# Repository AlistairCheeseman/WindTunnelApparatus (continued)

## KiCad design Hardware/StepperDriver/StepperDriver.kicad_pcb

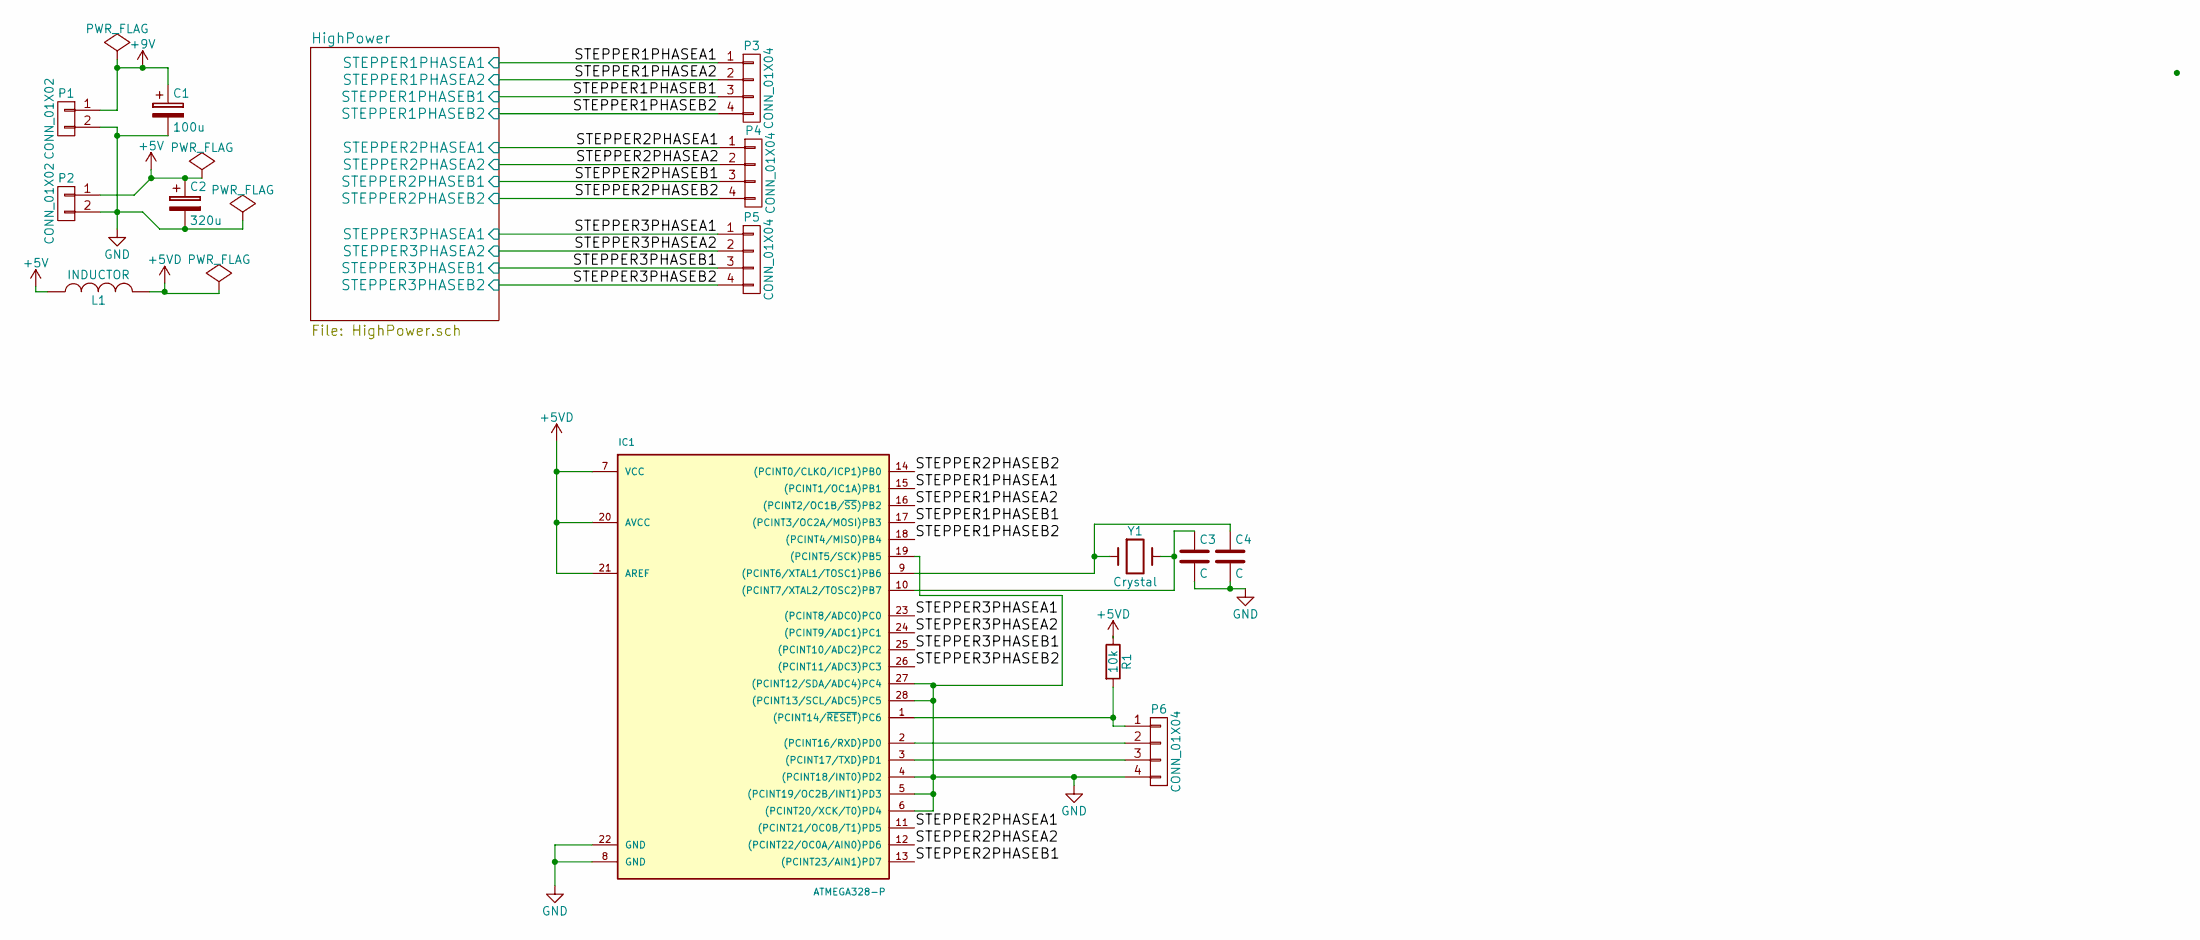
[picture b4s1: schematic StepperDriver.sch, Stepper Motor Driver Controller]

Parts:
C1: 100u; C_Radial_D10_L20_P7.5
C2: 320u; C_Radial_D10_L20_P7.5
C3, C4: C; C_Disc_D3_P2.5
IC1: ATMEGA328-P; DIP-28_W7.62mm_LongPads
L1: INDUCTOR; Neosid_Inductor_Sd12k-style3
P1, P2: CONN_01X02; TerminalBlock_Pheonix_MPT-2.54mm_2pol
P3, P4, P5, P6: CONN_01X04; TerminalBlock_Pheonix_MPT-2.54mm_4pol
R1: 10k; Resistor_Horizontal_RM10mm
Y1: Crystal; Crystal_HC48-U_Vertical

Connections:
+5V: C2.1, L1.1, P2.1; also elsewhere on the board
+5VD: IC1.7 (VCC), IC1.20 (AVCC), IC1.21 (AREF), L1.2, R1.1
+9V: C1.1, P1.1; also elsewhere on the board
/HighPower/STEPPER1PHASEA1: IC1.15 ((PCINT1/OC1A)PB1), P3.1; also elsewhere on the board
/HighPower/STEPPER1PHASEA2: IC1.16 ((PCINT2/OC1B/~SS~)PB2), P3.2; also elsewhere on the board
/HighPower/STEPPER1PHASEB1: IC1.17 ((PCINT3/OC2A/MOSI)PB3), P3.3; also elsewhere on the board
/HighPower/STEPPER1PHASEB2: IC1.18 ((PCINT4/MISO)PB4), P3.4; also elsewhere on the board
/HighPower/STEPPER2PHASEA1: IC1.11 ((PCINT21/OC0B/T1)PD5), P4.1; also elsewhere on the board
/HighPower/STEPPER2PHASEA2: IC1.12 ((PCINT22/OC0A/AIN0)PD6), P4.2; also elsewhere on the board
/HighPower/STEPPER2PHASEB1: IC1.13 ((PCINT23/AIN1)PD7), P4.3; also elsewhere on the board
/HighPower/STEPPER2PHASEB2: IC1.14 ((PCINT0/CLKO/ICP1)PB0), P4.4; also elsewhere on the board
/HighPower/STEPPER3PHASEA1: IC1.23 ((PCINT8/ADC0)PC0), P5.1; also elsewhere on the board
/HighPower/STEPPER3PHASEA2: IC1.24 ((PCINT9/ADC1)PC1), P5.2; also elsewhere on the board
/HighPower/STEPPER3PHASEB1: IC1.25 ((PCINT10/ADC2)PC2), P5.3; also elsewhere on the board
/HighPower/STEPPER3PHASEB2: IC1.26 ((PCINT11/ADC3)PC3), P5.4; also elsewhere on the board
GND: C1.2, C2.2, C3.2, C4.2, IC1.4 ((PCINT18/INT0)PD2), IC1.5 ((PCINT19/OC2B/INT1)PD3), IC1.6 ((PCINT20/XCK/T0)PD4), IC1.8 (GND), IC1.19 ((PCINT5/SCK)PB5), IC1.22 (GND), IC1.27 ((PCINT12/SDA/ADC4)PC4), IC1.28 ((PCINT13/SCL/ADC5)PC5), P1.2, P2.2, P6.4; also elsewhere on the board
unnamed: C3.1, IC1.10 ((PCINT7/XTAL2/TOSC2)PB7), Y1.2
unnamed: C4.1, IC1.9 ((PCINT6/XTAL1/TOSC1)PB6), Y1.1
unnamed: IC1.1 ((PCINT14/~RESET~)PC6), P6.1, R1.2
unnamed: IC1.2 ((PCINT16/RXD)PD0), P6.2
unnamed: IC1.3 ((PCINT17/TXD)PD1), P6.3

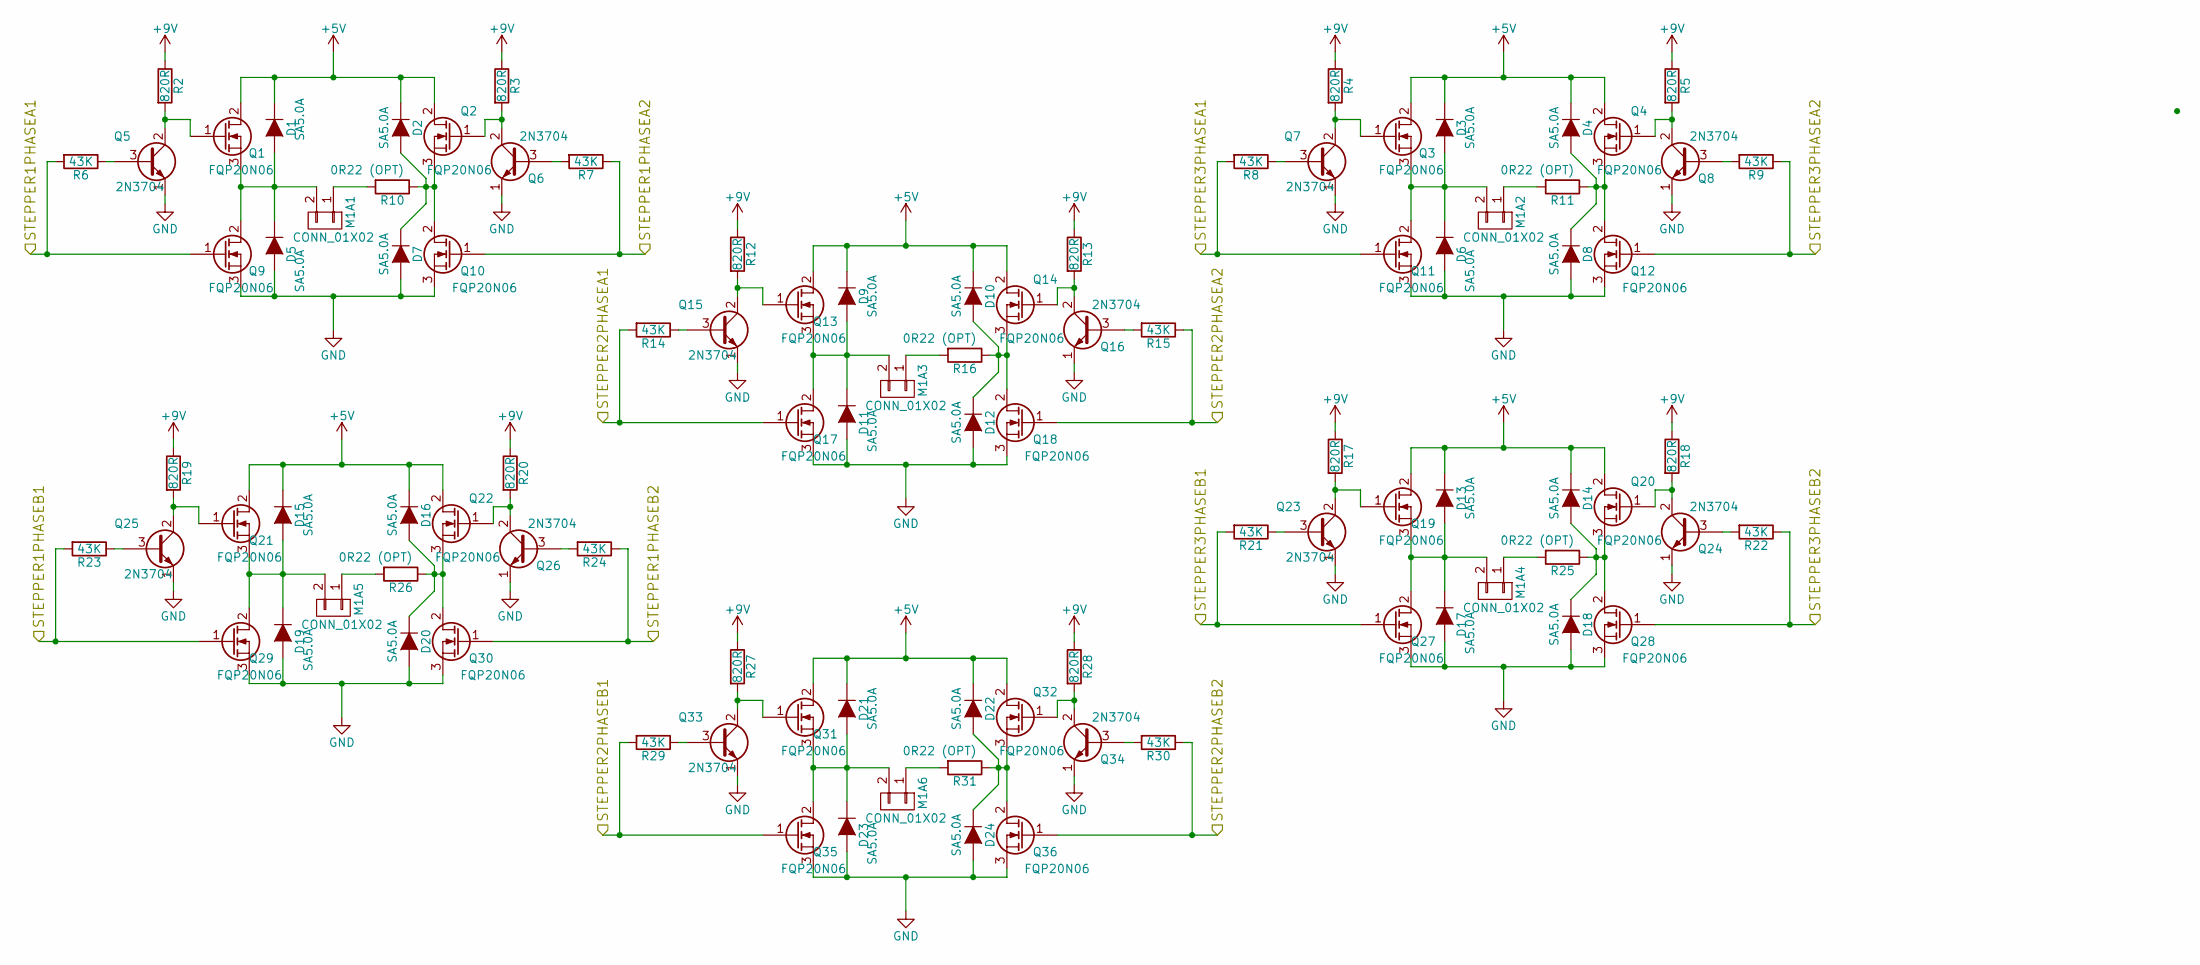
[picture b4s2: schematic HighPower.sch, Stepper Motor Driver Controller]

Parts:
D1, D2, D3, D4, D5, D6, D7, D8, D9, D10, D11, D12, D13, D14, D15, D16, D17, D18, D19, D20, D21, D22, D23, D24: SA5.0A; Diode_DO-35_SOD27_Horizontal_RM10
M1A1, M1A2, M1A3, M1A4, M1A5, M1A6: CONN_01X02; TerminalBlock_Pheonix_MPT-2.54mm_2pol
Q1, Q2, Q3, Q4, Q9, Q10, Q11, Q12, Q13, Q14, Q17, Q18, Q19, Q20, Q21, Q22, Q27, Q28, Q29, Q30, Q31, Q32, Q35, Q36: FQP20N06; TO-220_Neutral123_Horizontal_Reverse_LargePads
Q5, Q6, Q7, Q8, Q15, Q16, Q23, Q24, Q25, Q26, Q33, Q34: 2N3704; OldSowjetaera_Transistor_Type-I_BigPads
R2, R3, R4, R5, R12, R13, R17, R18, R19, R20, R27, R28: 820R; Resistor_Horizontal_RM10mm
R6, R7, R8, R9, R14, R15, R21, R22, R23, R24, R29, R30: 43K; Resistor_Horizontal_RM10mm
R10, R11, R16, R25, R26, R31: 0R22 (OPT); Resistor_Cement_KOA-BGR-3N

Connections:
+5V: D1.1 (K), D2.1 (K), D3.1 (K), D4.1 (K), D9.1 (K), D10.1 (K), D13.1 (K), D14.1 (K), D15.1 (K), D16.1 (K), D21.1 (K), D22.1 (K), Q1.2 (D), Q2.2 (D), Q3.2 (D), Q4.2 (D), Q13.2 (D), Q14.2 (D), Q19.2 (D), Q20.2 (D), Q21.2 (D), Q22.2 (D), Q31.2 (D), Q32.2 (D); also elsewhere on the board
+9V: R2.1, R3.1, R4.1, R5.1, R12.1, R13.1, R17.1, R18.1, R19.1, R20.1, R27.1, R28.1; also elsewhere on the board
/HighPower/STEPPER1PHASEA1: Q9.1 (G), R6.2; also elsewhere on the board
/HighPower/STEPPER1PHASEA2: Q10.1 (G), R7.1; also elsewhere on the board
/HighPower/STEPPER1PHASEB1: Q29.1 (G), R23.2; also elsewhere on the board
/HighPower/STEPPER1PHASEB2: Q30.1 (G), R24.1; also elsewhere on the board
/HighPower/STEPPER2PHASEA1: Q17.1 (G), R14.2; also elsewhere on the board
/HighPower/STEPPER2PHASEA2: Q18.1 (G), R15.1; also elsewhere on the board
/HighPower/STEPPER2PHASEB1: Q35.1 (G), R29.2; also elsewhere on the board
/HighPower/STEPPER2PHASEB2: Q36.1 (G), R30.1; also elsewhere on the board
/HighPower/STEPPER3PHASEA1: Q11.1 (G), R8.2; also elsewhere on the board
/HighPower/STEPPER3PHASEA2: Q12.1 (G), R9.1; also elsewhere on the board
/HighPower/STEPPER3PHASEB1: Q27.1 (G), R21.2; also elsewhere on the board
/HighPower/STEPPER3PHASEB2: Q28.1 (G), R22.1; also elsewhere on the board
GND: D5.2 (A), D6.2 (A), D7.2 (A), D8.2 (A), D11.2 (A), D12.2 (A), D17.2 (A), D18.2 (A), D19.2 (A), D20.2 (A), D23.2 (A), D24.2 (A), Q5.1 (E), Q6.1 (E), Q7.1 (E), Q8.1 (E), Q9.3 (S), Q10.3 (S), Q11.3 (S), Q12.3 (S), Q15.1 (E), Q16.1 (E), Q17.3 (S), Q18.3 (S), Q23.1 (E), Q24.1 (E), Q25.1 (E), Q26.1 (E), Q27.3 (S), Q28.3 (S), Q29.3 (S), Q30.3 (S), Q33.1 (E), Q34.1 (E), Q35.3 (S), Q36.3 (S); also elsewhere on the board
unnamed: D1.2 (A), D5.1 (K), M1A1.2, Q1.3 (S), Q9.2 (D)
unnamed: D2.2 (A), D7.1 (K), Q2.3 (S), Q10.2 (D), R10.1
unnamed: D3.2 (A), D6.1 (K), M1A2.2, Q3.3 (S), Q11.2 (D)
unnamed: D4.2 (A), D8.1 (K), Q4.3 (S), Q12.2 (D), R11.1
unnamed: D10.2 (A), D12.1 (K), Q14.3 (S), Q18.2 (D), R16.1
unnamed: D9.2 (A), D11.1 (K), M1A3.2, Q13.3 (S), Q17.2 (D)
unnamed: D13.2 (A), D17.1 (K), M1A4.2, Q19.3 (S), Q27.2 (D)
unnamed: D14.2 (A), D18.1 (K), Q20.3 (S), Q28.2 (D), R25.1
unnamed: D15.2 (A), D19.1 (K), M1A5.2, Q21.3 (S), Q29.2 (D)
unnamed: D16.2 (A), D20.1 (K), Q22.3 (S), Q30.2 (D), R26.1
unnamed: D21.2 (A), D23.1 (K), M1A6.2, Q31.3 (S), Q35.2 (D)
unnamed: D22.2 (A), D24.1 (K), Q32.3 (S), Q36.2 (D), R31.1
unnamed: M1A1.1, R10.2
unnamed: M1A2.1, R11.2
unnamed: M1A3.1, R16.2
unnamed: M1A4.1, R25.2
unnamed: M1A5.1, R26.2
unnamed: M1A6.1, R31.2
unnamed: Q1.1 (G), Q5.2 (C), R2.2
unnamed: Q2.1 (G), Q6.2 (C), R3.2
unnamed: Q3.1 (G), Q7.2 (C), R4.2
unnamed: Q4.1 (G), Q8.2 (C), R5.2
unnamed: Q5.3 (B), R6.1
unnamed: Q6.3 (B), R7.2
unnamed: Q7.3 (B), R8.1
unnamed: Q8.3 (B), R9.2
unnamed: Q13.1 (G), Q15.2 (C), R12.2
unnamed: Q14.1 (G), Q16.2 (C), R13.2
unnamed: Q15.3 (B), R14.1
unnamed: Q16.3 (B), R15.2
unnamed: Q19.1 (G), Q23.2 (C), R17.2
unnamed: Q20.1 (G), Q24.2 (C), R18.2
unnamed: Q21.1 (G), Q25.2 (C), R19.2
unnamed: Q22.1 (G), Q26.2 (C), R20.2
unnamed: Q23.3 (B), R21.1
unnamed: Q24.3 (B), R22.2
unnamed: Q25.3 (B), R23.1
unnamed: Q26.3 (B), R24.2
unnamed: Q31.1 (G), Q33.2 (C), R27.2
unnamed: Q32.1 (G), Q34.2 (C), R28.2
unnamed: Q33.3 (B), R29.1
unnamed: Q34.3 (B), R30.2

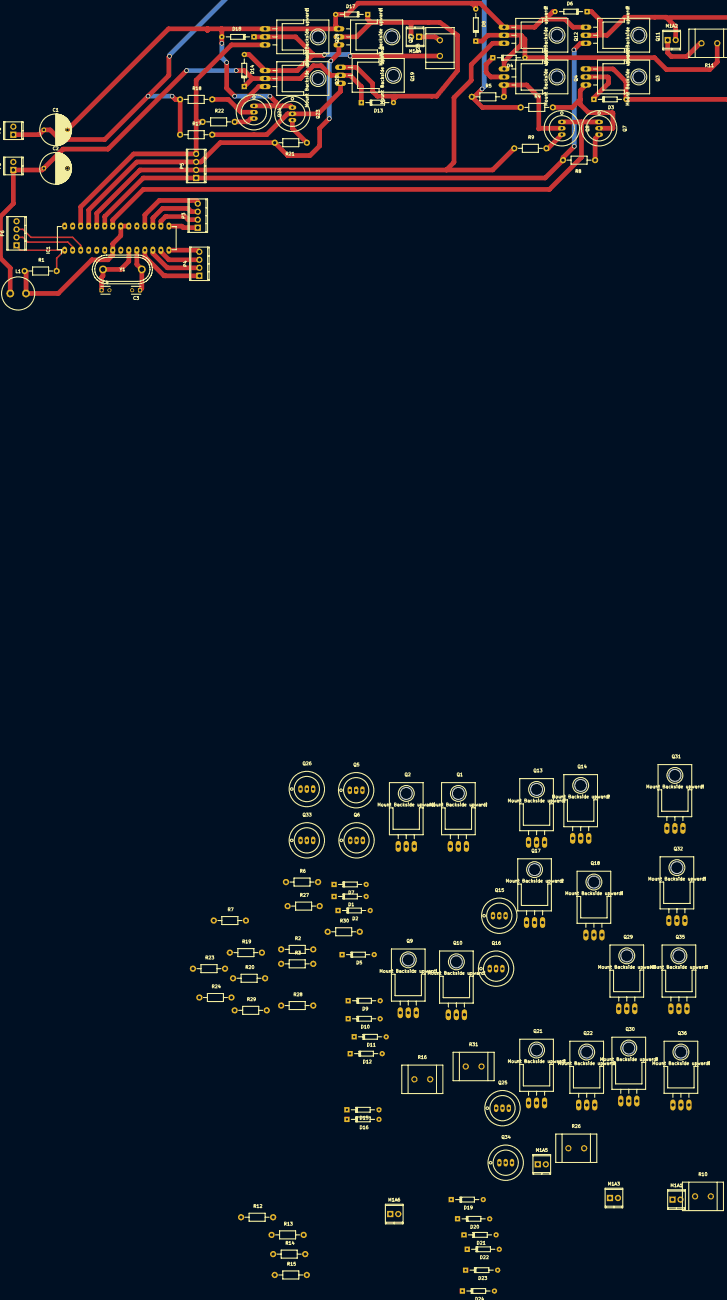
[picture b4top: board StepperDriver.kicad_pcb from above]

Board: 2 copper layers, 110 parts (0 on the bottom side), 63 nets.

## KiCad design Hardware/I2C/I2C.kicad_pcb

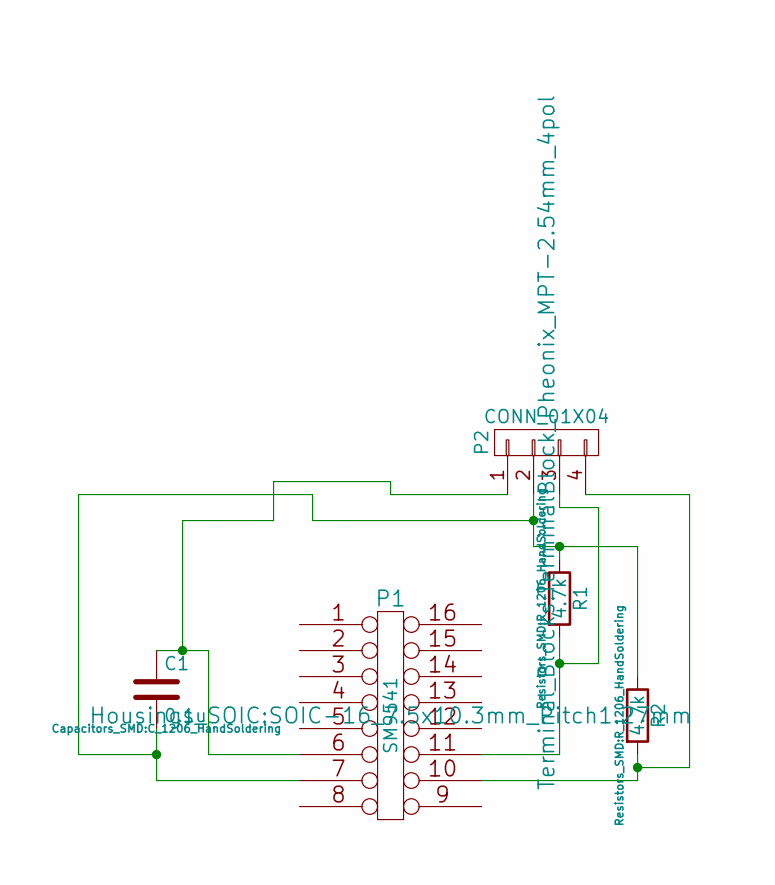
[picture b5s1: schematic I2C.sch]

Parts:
C1: 0.1u; C_1206_HandSoldering
P1: SM9541; SOIC-16_7.5x10.3mm_Pitch1.27mm
P2: CONN_01X04; TerminalBlock_Pheonix_MPT-2.54mm_4pol
R1, R2: 4.7k; R_1206_HandSoldering

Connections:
unnamed: C1.1, P1.6, P2.1
unnamed: C1.2, P1.7, P2.2, R1.1, R2.1
unnamed: P1.10, P2.4, R2.2
unnamed: P1.11, P2.3, R1.2

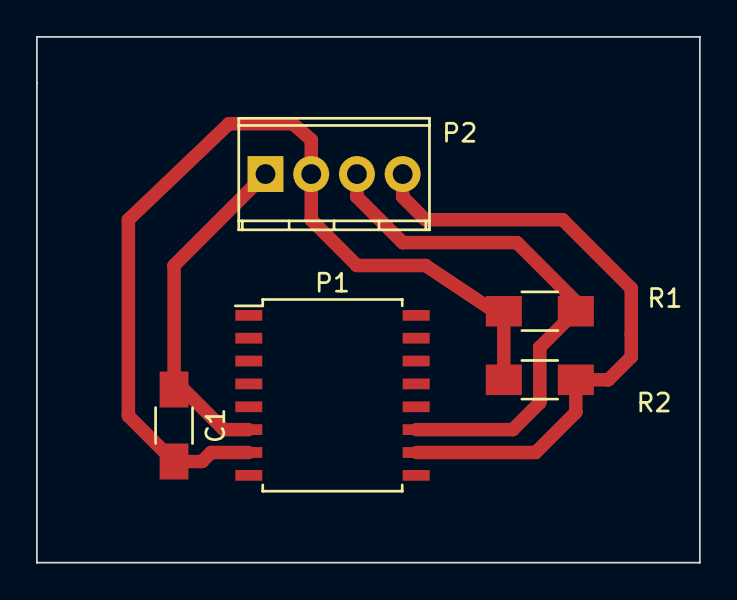
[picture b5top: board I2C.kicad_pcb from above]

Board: 2 copper layers, 36.8 x 29.2 mm, 5 parts (0 on the bottom side), 4 nets.

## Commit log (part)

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2015-11-17 initial commit of Serial Throughput tester
2015-11-17 updated folder structure to three main categories, software, hardware and firmware
2015-11-17 added Arduino Example of simple stepper motor control
2015-11-17 added intial Datasheets used
2015-11-17 tidied directory structure
2015-11-17 created simple TCP Echo example sourced from: https://reference.digilentinc.com/nexys:nexys4:gsmbs
2015-11-17 created initial TCP Test program
2015-11-17 created simple TCP throughput server test NOTE: UPDATE IP ADDRESS TO WORK
2015-11-17 created intial I2C mockup for SLM9541
2015-11-17 updated echo example to new file location
2015-11-17 updated TCP Test Project naming
2015-11-17 created the initial Main software control solution. only created a UI and the shell host program
2015-11-17 created .gitignore and .gitattributes for Visual Studio Projects
2015-11-17 removed webtalk data and reverted back to vivado 2012.2
2015-11-17 added a few extra folders to the gitignore for FPGA work.
2015-11-17 Updated readme text
2015-11-17 updated project file
2015-11-18 created simple host udp test program
2015-11-23 created simple program to read pressure transducer on an arduino
2015-11-23 added additional DataSheets
2015-11-23 created -15V line and 7.5mm resistor custom parts
2015-11-23 added pure c++ application to determine speeds on a lower programming level, to determine if c# is causing slowdown, additionally updated c# program to work with iperf packets
2015-11-23 imported Serial Charter example from personal store for adaptation.
2015-11-23 begun work on hot wire schematic
2015-11-23 created simple UDP test project with packets usable by iperf. using two versions of application, one taken from xilinx application notes - xapp1026
2015-11-25 removed unneeded resources files
2015-11-25 updated to net framework 4.5
2015-11-25 addded simple export start stop functions
2015-11-26 added some basic features to serial comms
2015-11-30 fixed missing packages.
2015-12-01 updated graph text. updated conversion to Pa
2015-12-03 moved from single stepper design to three different types of stepping
2015-12-03 updated schematic for 2 motors
2015-12-03 updated window for better data processing ( some simple sanity checks)
2015-12-03 added component values. Updated for 3 motor design
2015-12-03 removed unneeded files
2015-12-03 added missing diode values, added motor connectors. Exported Schematic to PDF
2015-12-06 created blank I2C test FPGA project
2016-01-17 initial mockup of single channel driver
2016-01-25 updated to modularised design and initial draft of production layout
2016-01-25 added various pictures of PCB
2016-01-26 created main project file for schematics. exported design files to pdf and dxf
2016-01-27 initial commit of bugged code
2016-01-28 tidied i2c hardware files
2016-01-28 updated to use more concise state model - issue with derived clock state machine
2016-02-02 fixed incorrect Xtal footprint
2016-02-03 created root project file - to make managing projects easier
2016-02-04 updated pins to match schematics updated delay variables to set max speed and min speed added initial command structure tidied serial init routine and default to wave drive stepper converted to micro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
2016-02-08 fixed incorrect initialisation value for half step tidied shift left operation ( added masking) added calculation of totalSteps - 400 or 200 per rev depending on mode fixed incorrect count of steps f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
2016-02-08 updated Firmware directory structure to better seperate tests from actual firmware
2016-02-09 added basic files for stepper motor control
2016-02-09 updated design to use correct state machine ( single SM tied to clock)
2016-02-09 Updated licence to GPL v3
2016-02-10 added quick and dirty keepout zones to the solder Resist layer added board identification text added alignment marks to other layers (solder resist + Silk)
2016-02-11 created Pressure transducer array project and updated baud to 2M baud.
2016-02-11 updated control interface to correct structure and removed stale project
2016-02-11 fixed clock typo
2016-02-11 removed default sensor data text
2016-02-11 removed incorrectly committed file
2016-02-12 made log file generate with timestamp to make sure unique. cleaned serial clean routine, setting filestream to null when finished. tidied buffer routine to prevent excess padding.
2016-02-12 updated console to print received data in hex
2016-02-18 discovered clock in bug, where data would not be updated quick enough for the data to be clocked in. Added new clockin state to get data and provide necessary delay fixed bug where serial ready flag 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
2016-02-18 increased serial speed to 2M - found anything slower would cause buffer overflow issues
2016-02-21 better defined motor enums
2016-02-21 created a Full step only firmware variant in meantime of the main software being developed.
2016-02-22 added silkscreen hole outline
2016-02-22 removed some stale display arrangements and tied up some of the UI
2016-02-22 moved from dispatcher driven threading to queue & worker process. Started using cleaner commands.
2016-02-23 removed old pressure calculation as results not accurate enough. made isConnected public. updated file dumps to have .DAT extensions. completely re-wrote data handling mechanism
2016-02-23 tied up pressure export and defaulted to fast jog of stepper
2016-02-23 tied up jog right button, added export process of pressure data.
2016-02-24 updated to get ALL data from sensor ( all 4 bytes)
2016-02-24 added state and implemented sensor id byte added to payload.
2016-02-25 temporarily removed unused ports. updated to use correct ports for SCL and SDA. Removed rw and addr from I2C control as constant so will not need changing.
2016-02-25 updated simulation to match new signal naming conventions
2016-02-26 updated Pressure Data class to more appropriate names, also added additional data elements. updated processing routine to process new 6 byte header.Also added better header handling - for future upda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
2016-02-26 updated to 10 transducer code. still needs testing.
2016-02-27 updated delay to be easier to edit and decreased delay.
2016-02-27 completely re-wrote to remove multiplexers. Seems to have stabilised the sensor array packets and removed a lot of warnings in synthesis.
2016-02-27 enabled multiple values for connection state.
2016-02-27 mods to stepper controller: removed unused dispatcher added ViewModelBase helper class converted isConnected and isBusy to properties with notifications
2016-02-27 added sensorId to pressureData class
2016-02-27 extracted speed routine to seperate subroutine to allow for easier modification
2016-02-27 added lastest sensor reading properties with update. added regions added connection state property with update. removed dispatcher allocation on creation and moved to set dispatcher routine added rou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
2016-02-27 indented class added update to make the controllers initialise on startup. added HotWireFunctions added notify property update routines
2016-03-01 updated project to use new file location
2016-03-01 added x and y position to stepper controller
2016-03-01 added x and y stepper info, removed excess hot wire readings.
2016-03-01 added moment (datetime reading) and Id (unique number) to pressure data class.
2016-03-01 created hotwire ADC pcb project
2016-03-02 created custom part for ADC component.
2016-03-02 completely re-worked data processing routine. routine now runs on two worker processes to crunch data. Increased OS receive buffer size.
2016-03-02 completely re-worked data sequencer to work better with 2+ sensors
2016-03-04 increased timeout window to prevent multiple loops, also removed timeout from sensor 1. this fixes timing of the loops, but means that sensor 1 will ALWAYS have to be connected
2016-03-04 updated to compile program as 64x
2016-03-04 updated calculations to use double instead of decimal to speed processing time. added additional worker to seperate data into packets. updated indents added queue status indicators
2016-03-11 moved HotWireADC hardware files to revision structure - due to complete design change
2016-03-12 created initial design and added relevant datasheets
2016-03-12 fixed incorrect sensor count update. made serialiser buffer bigger fixed typo on temperature calculation
2016-03-13 created intial PCB layout
2016-03-13 moved external reference to BNC connector & tidied layout
2016-03-13 updated regulator footprint and removed additional regulator
2016-03-13 increased track widths.
2016-03-14 added parts needed for BOM + parts from other HotWire hardware ( maintained by different user)
2016-03-14 tidied layout added text to silk added mounting holes and alignment marks
2016-03-15 added datasheet for high side driver transistor
2016-03-15 added datasheet for DC barrel connector
2016-03-17 added position updates to stepper controller firmware
2016-03-17 added infographic to solution and added stimulus generator to project- hardcoded for 10%
2016-03-17 meade measurements public
2016-03-17 added positional updates to stepper controller. Added gotoXY support.
2016-03-17 added automationcontroller class to mainviewmodel. added measurement information properties. added Loadstimulus and executemeasurementcycle functions
2016-03-17 added clause to ensure that no steps are taken on a 0 step command.
2016-03-17 updated loop counts to ensure accurate step counts
2016-03-17 updated positional data to read in microns fixed axis typo. set motor to not move after axis zero.
2016-03-17 moved controllers to automation container. made automationcontroller use background worker to keep UI thread responsive. moved some properties to the automationcontroller
2016-03-19 updated published version
2016-03-28 added clearer zero command
2016-03-28 updated to routine to correctly work according to step distance
2016-03-28 updated binding expressions to be more uniform and complete.
2016-03-28 moved data containers to DataClasses. made clearer regions in class. Added completion events
2016-03-28 plugged into automation event.
2016-03-28 created c++ programs to simulate the sensors
2016-03-28 updated gitignore for c++ projects
2016-03-31 removed unneeded comments/debug info
2016-03-31 added queue status to menu form
2016-03-31 added simple interrupt script example for potential expansion of stepper controller
2016-04-03 moved export data to central DataClasses - moved export preperation to static routine to expose for automation controller
2016-04-03 created basic full export routine - to be tested
2016-04-03 added new parameter to ui - time for flow to settle
2016-04-03 updated ui to show units
2016-04-03 updated gitignore for VS2015R2
2016-04-03 updated stimulus generator routine to export settle time.
2016-04-04 increased serial speed. added fix to ask for limit location when initialising
2016-04-04 added default values for this particular wind tunnel
2016-04-04 updated stepper baud rate and updated a lot of hard coded values to constants. added limit location functionality. fixed Y axis direction issue.
2016-04-04 added details to serial port exception. implelented a start value to the export sorter function
2016-04-04 updated dialog to remove file extensio values. also added alert to show export completed.
2016-04-04 added busy flag to automation controller. took advantage of pressure export id continuation function. fixed missing delimeter on export. added check to prevent creation of empty files.
2016-04-04 updated file types and added wired up automation cancel button
2016-04-06 created smd jack in library
2016-04-06 updated schematic to use correct DC jack footprint
2016-04-07 shortened acceleration time in stepper algorithm
2016-04-07 added enviromental conditions box to UI
2016-04-10 updated export routine to use array access instead of foreach as foreach cannot handle large numbers of records. added trap to only record data if a variable is true if not it just updates the UI.
2016-04-10 added atmospheric pressures and temperatures to VM and export. removed background worker and replaced with async method to get better timing of system. changed from foreach to index array addressing 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
    Updated UI to use new async automation method.
2016-04-10 ensured current sensor readings - by setting readings to 0 before processing readings recreated queue to allow for re-connections
2016-04-10 FIXED MASSIVE BUG IN EXPORT DATA ROUTINE
2016-04-11 added extra marks and alignment to PCB for silkscreen
2016-04-15 increased delay to increase torque to motor.
2016-04-15 updated option button typo. updated initial positions
2016-04-15 added pause capability. Added check to only request to update stepper motors if needed. move sensor acquisition to try catch expression to recover from bad readings
